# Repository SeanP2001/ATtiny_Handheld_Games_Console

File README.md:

# ATtiny Handheld Games Console

## Table of Contents

- [Introduction](#introduction)
- [Circuitry](#circuitry)
  * [Schematic](#schematic)
  * [PCB Design](#pcb-design)
    + [Button Footprints](#button-footprints)
    + [Display Pinout Jumpers](#display-pinout-jumpers)
  * [Soldered PCB](#soldered-pcb)
- [Board Manager & Programming Setup](#board-manager---programming-setup)
- [Code](#code)
- [Enclosure](#enclosure)
  * [CAD Enclosure](#cad-enclosure)
  * [3D Printed Enclosure](#3d-printed-enclosure)
- [Game Library](#game-library)
- [Further Work](#further-work)
  * [Version 2 - Featuring the Pico](#version-2---featuring-the-pico)

## Introduction

My aim is to create a handheld games console, based on the ATtiny85 AVR microcontroller. Users will be able to program their own games and play them anywhere. The long-term goal for this project is to create a library of games, and it would be amazing to build a community of users who can upload their games for others to download and play.

## Circuitry

### Schematic

### PCB Design

|  |  |
| ------------------------------------------------ | ----------------------------------------------------- |
|                    |                    |

#### Button Footprints

I designed the button footprint to give the option of using either tactile buttons or silicone button membranes. However, after experimenting I have found that silicone buttons will never work with this design. The analog value recieved by the microcontroller varies wildly depending on the pressure applied to the button. This makes silicone buttons unusable. **Please use tactile buttons when assembling the PCB**. In the next PCB revision, I intend to remove the contact pads and return to a regular tactile button footprint.

#### Display Pinout Jumpers

Another feature of the PCB is the jumper connections under the display. The I2C OLED displays do not all have the same pin layout. When you buy a display online, the item you recieve may not have the same pinout as the one in the photos. Due to this inconsistency I have designed the board to work with both pinouts. If your display has the pinout (in order) Vcc/GND/SCL/SDA then you need to use solder to bridge the middle pads to the upper pads (shown blue below). If it is GND/Vcc/SCL/SDA then you need to bridge the middle pads to the lower pads (shown red below). Once you have done this, use Kapton tape to insulate the solder bridges and prevent them from causing a short circuit on the back of the display.

### Soldered PCB

## Board Manager & Programming Setup

I am using the ATTinyCore board manager ([GitHub - SpenceKonde/ATTinyCore: Arduino core for ATtiny 1634, 828, x313, x4, x41, x5, x61, x7 and x8](https://github.com/SpenceKonde/ATTinyCore)) with the following settings:

Currently I am programming the ATtiny using an Arduino Uno as a programmer. You could either do this or use a dedicated ISP programmer.

## Code

This repostitory includes code to test that the buttons and display are working correctly. When you press a button the display should show the analog value on the actionButton and directionButton pins, along with the name of the button pressed. Recognised buttons are as follows:

- UP

- DOWN

- LEFT

- RIGHT

- UP_LEFT

- UP_RIGHT

- DOWN_LEFT

- DOWN_RIGHT

- A

- B

## Enclosure

### CAD Enclosure

### 3D Printed Enclosure

|  |  |  |
| --------------------------------------- | ---------------------------------------- | ---------------------------------------- |

## Game Library

This is where you can find all of the games made for the console.

- [Astro Barrier](https://github.com/SeanP2001/ATtiny_Astro_Barrier)
- [Snake](https://github.com/SeanP2001/ATtiny_Snake)

## Further Work

Next time I order PCBs I will remove the contact pads and return to a regular tactile button footprint. I will also remove the silicone button membranes and alignment pins from the enclosure design. I may make small alterations to the height of the buttons along with minimising the gaps around the volume wheel and on/off switch.

### Version 2 - Featuring the Pico

I have realised that this project is not as accessible as I would like. Programming an ATtiny could be a complicated and off-putting task for a beginner. The initial goal of this project was to make a platform for people to practice programming. 

To make a more accessible platform I think I need to switch to using a USB programmable board. An ideal candidate for this is the Raspberry Pi Pico because you can just plug it into your computer and program it using MicroPython or C++. 

However, using the Pico brings it's own challenges. For instance:

- Not all Arduino libraries are compatible (might be fixable with a compatability layer)

- A coin cell battery will no longer be adequate

- You cannot change games without re-programming the board

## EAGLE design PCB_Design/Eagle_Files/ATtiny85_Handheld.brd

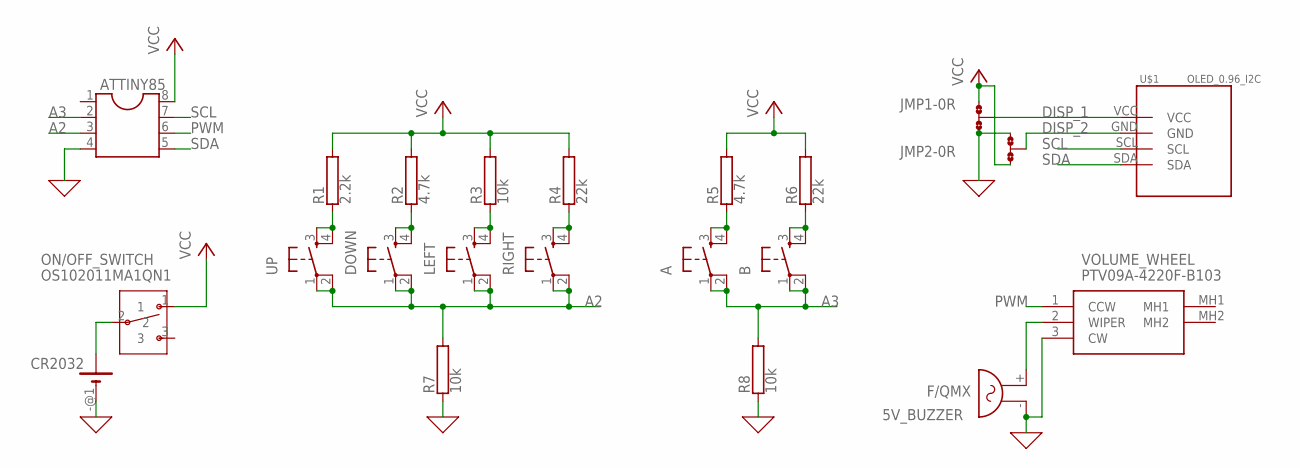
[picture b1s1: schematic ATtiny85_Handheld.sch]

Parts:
5V_BUZZER: F/QMX
A: TACTILE/SILICONE_BUTTON
ATTINY85: DIL8; DIL08
B: TACTILE/SILICONE_BUTTON
CR2032: CR2032_BATTERY_HOLDER
DOWN: TACTILE/SILICONE_BUTTON
JMP1, JMP2: 0R-JUMPA; A0R-JMP
LEFT: TACTILE/SILICONE_BUTTON
ON/OFF_SWITCH: OS102011MA1QN1
R1: 2.2k; AC01
R2, R5: 4.7k; AC01
R3, R7, R8: 10k; AC01
R4, R6: 22k; AC01
RIGHT: TACTILE/SILICONE_BUTTON
U$1: OLED_0.96_I2C
UP: TACTILE/SILICONE_BUTTON
VOLUME_WHEEL: PTV09A-4220F-B103; PTV09A4220FB103

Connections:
A2: ATTINY85.3, DOWN.1, DOWN.2 (P1), LEFT.1, LEFT.2 (P1), R7.2, RIGHT.1, RIGHT.2 (P1), UP.1, UP.2 (P1)
A3: A.1, A.2 (P1), ATTINY85.2, B.1, B.2 (P1), R8.2
DISP_1: JMP1.2, U$1.VCC
DISP_2: JMP2.2, U$1.GND
GND: 5V_BUZZER.- (1), ATTINY85.4, CR2032.-@1 (-), JMP1.3, JMP2.1, R7.1, R8.1, VOLUME_WHEEL.3 (CW)
unnamed: CR2032.+@4 (+), ON/OFF_SWITCH.2
unnamed: R4.1, RIGHT.3 (S), RIGHT.4 (S1)
unnamed: LEFT.3 (S), LEFT.4 (S1), R3.1
unnamed: DOWN.3 (S), DOWN.4 (S1), R2.1
unnamed: R1.1, UP.3 (S), UP.4 (S1)
unnamed: A.3 (S), A.4 (S1), R5.1
unnamed: B.3 (S), B.4 (S1), R6.1
unnamed: 5V_BUZZER.+ (2), VOLUME_WHEEL.2 (WIPER)
PWM: ATTINY85.6, VOLUME_WHEEL.1 (CCW)
SCL: ATTINY85.7, U$1.SCL
SDA: ATTINY85.5, U$1.SDA
VCC: ATTINY85.8, JMP1.1, JMP2.3, ON/OFF_SWITCH.1, R1.2, R2.2, R3.2, R4.2, R5.2, R6.2

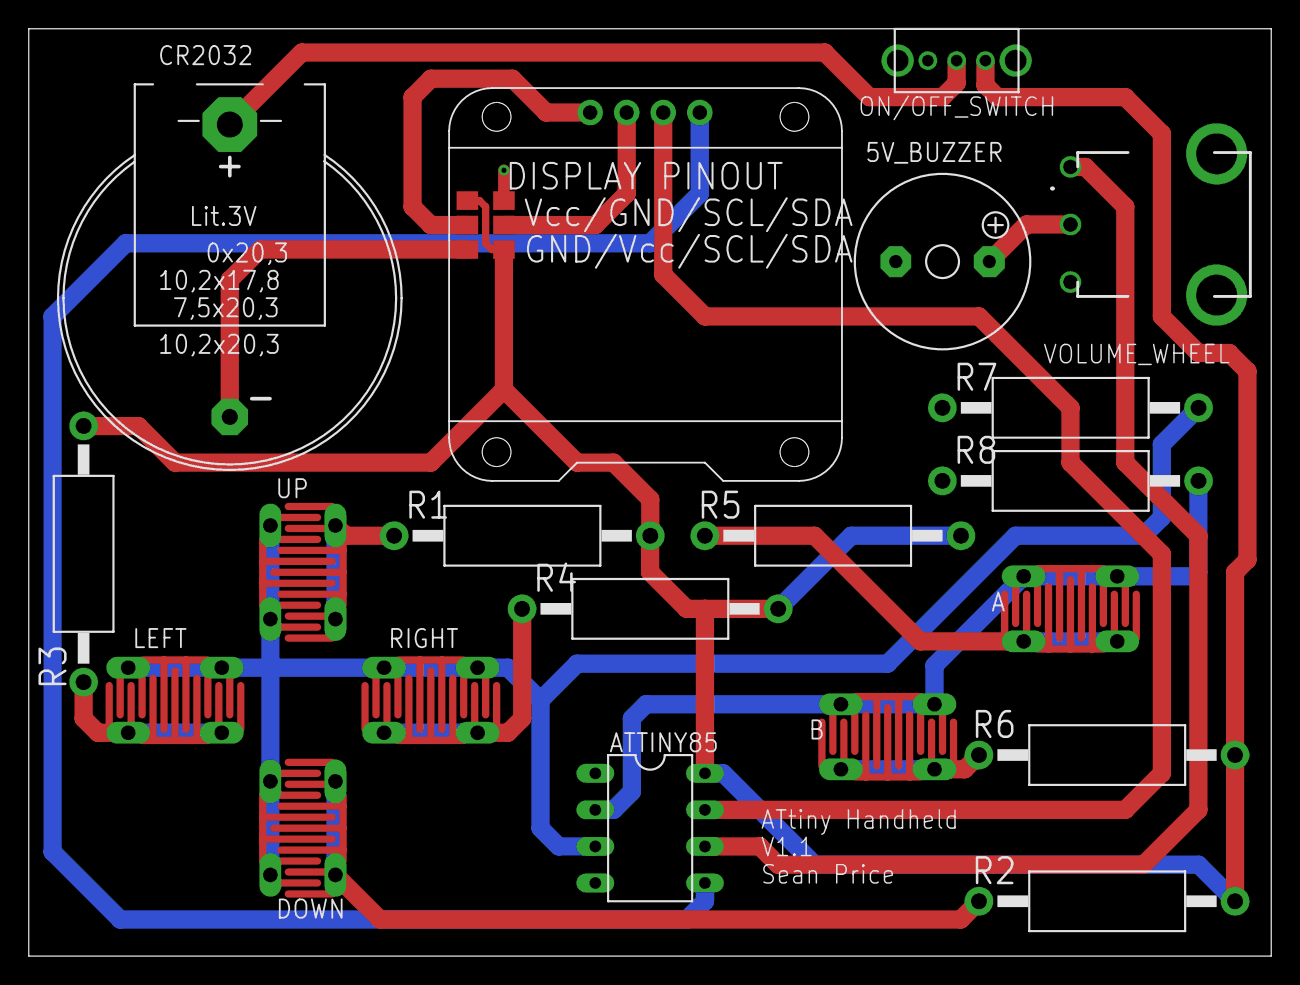
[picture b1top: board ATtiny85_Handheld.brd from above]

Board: 2 copper layers, 86.3 x 64.4 mm, 22 parts (0 on the bottom side), 17 nets.

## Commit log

2022-02-27 V0.1.0 Added PCB files, code to test the PCB and updated README.md
2022-03-13 V0.2.0 Created 3D model of the populated PCB
2022-03-20 V1.0.0 Added enclosure CAD files and updated README.md
2022-05-25 V1.1.0 Added Snake to the game library
2022-06-02 V1.2.0 Updated the PCB to V1.1
    - Option of using silicone or tactile buttons
    - Removed D1
    - Hand-router, thicker traces
    - Broke the schematic into sections to make it easier to follow
    - Update/fixed the battery holder footprint
    - Changed the switch footprint to use an angled slide switch
2022-06-07 Finalised PCB V1.1
2022-06-07 V1.2.1 Finalised PCB V1.1
2022-08-21 V1.3.0 Updated the enclosure to fit PCB V1.1
    - Choice between using tactile or silicone buttons (both STL files available)
2022-08-21 V1.3.1 Fixed left button not being recognised
2022-08-21 V1.4.0 Updated README.md
2022-09-05 V1.4.1 Removed Old PCB 3D Files
2022-09-14 V1.4.2 Added LICENSE.md
2022-09-23 V1.4.3 Added Libraries
